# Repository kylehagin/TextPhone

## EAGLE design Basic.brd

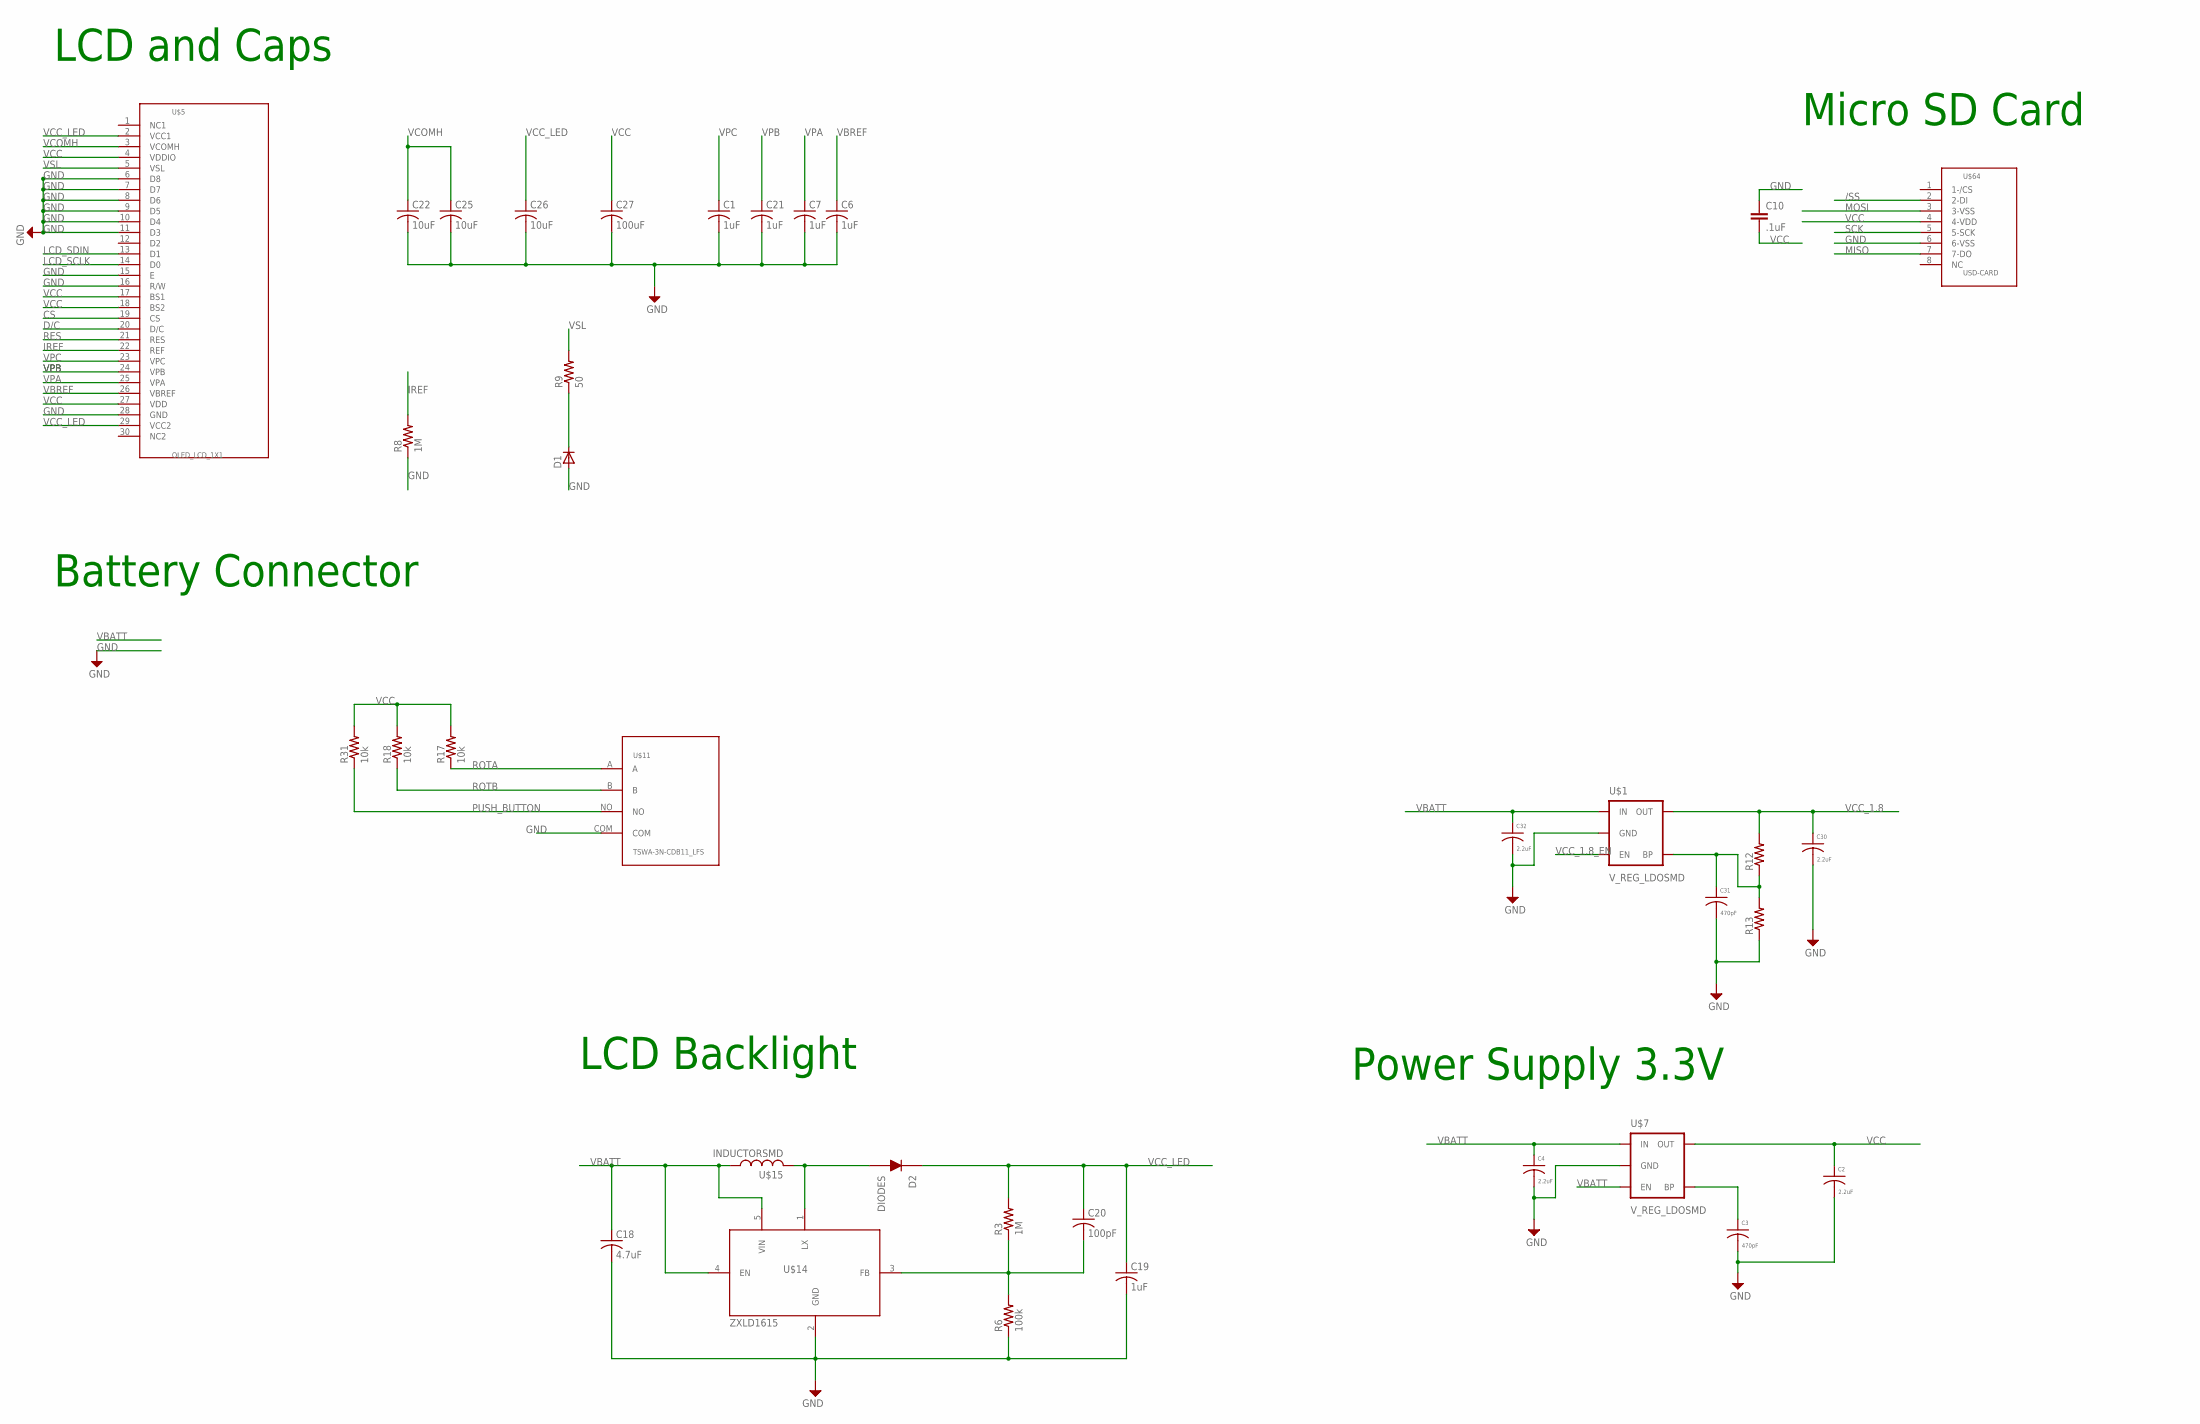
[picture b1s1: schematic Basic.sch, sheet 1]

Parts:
C1, C6, C7, C21: 1uF; C0402
C2, C4: 2.2uF; C0402
C3, C31: 470pF; C0402
C10: .1uF; C0402
C18: 4.7uF; C0805K
C19: 1uF; C1206
C20: 100pF; C0402
C22, C25, C26: 10uF; C0603
C27: 100uF; C0603
C30, C32: 2.2uF; C0603
D1: D-SOD123; SOD123
D2: DIODES; SOD-123
R3: 1M; R0805
R6: 100k; R0805
R8: 1M; R0603
R9: 50; R0603
R12, R13: R-US_R0402; R0402
R17, R18, R31: 10k; R0402
U$1, U$7: V_REG_LDOSMD; SOT23-5
U$5: OLED_LCD_1X1; 30ZIF
U$11: TSWA-3N-CDB11_LFS; TSWA-3N-CB11_LFS
U$14: ZXLD1615; SOT23-5L
U$15: INDUCTORSMD; INDUCTORSMD1
U$64: USD-CARD; 502774-0891

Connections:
/SS: U$64.2 (2-DI); also elsewhere on the board
CS: U$5.19 (CS); also elsewhere on the board
D/C: U$5.20 (D/C); also elsewhere on the board
GND: C1.2, C2.2, C3.2, C4.2, C6.2, C7.2, C10.1, C18.2, C19.2, C21.2, C22.2, C25.2, C26.2, C27.2, C30.2, C31.2, C32.2, D1.2 (A), R6.1, R8.1, R13.1, U$1.2 (GND), U$5.6 (D8), U$5.7 (D7), U$5.8 (D6), U$5.9 (D5), U$5.10 (D4), U$5.11 (D3), U$5.15 (E), U$5.16 (R/W), U$5.28 (GND), U$7.2 (GND), U$11.COM, U$14.2 (GND), U$64.6 (6-VSS); also elsewhere on the board
IREF: R8.2, U$5.22 (REF)
LCD_SCLK: U$5.14 (D0); also elsewhere on the board
LCD_SDIN: U$5.13 (D1); also elsewhere on the board
MISO: U$64.7 (7-DO); also elsewhere on the board
MOSI: U$64.3 (3-VSS); also elsewhere on the board
unnamed: C3.1, U$7.4 (BP)
unnamed: C20.2, R3.1, R6.2, U$14.3 (FB)
unnamed: D1.1 (C), R9.1
unnamed: D2.1 (A1), U$14.1 (LX), U$15.2
unnamed: C31.1, R12.1, R13.2, U$1.4 (BP)
PUSH_BUTTON: R31.1, U$11.NO; also elsewhere on the board
RES: U$5.21 (RES); also elsewhere on the board
ROTA: R17.1, U$11.A; also elsewhere on the board
ROTB: R18.1, U$11.B; also elsewhere on the board
SCK: U$64.5 (5-SCK); also elsewhere on the board
VBATT: C4.1, C18.1, C32.1, U$1.1 (IN), U$7.1 (IN), U$7.3 (EN), U$14.4 (EN), U$14.5 (VIN), U$15.1; also elsewhere on the board
VBREF: C6.1, U$5.26 (VBREF)
VCC: C2.1, C10.2, C27.1, R17.2, R18.2, R31.2, U$5.4 (VDDIO), U$5.17 (BS1), U$5.18 (BS2), U$5.27 (VDD), U$7.5 (OUT), U$64.4 (4-VDD); also elsewhere on the board
VCC_1.8: C30.1, R12.2, U$1.5 (OUT); also elsewhere on the board
VCC_1.8_EN: U$1.3 (EN); also elsewhere on the board
VCC_LED: C19.1, C20.1, C26.1, D2.2 (C), R3.2, U$5.2 (VCC1), U$5.29 (VCC2)
VCOMH: C22.1, C25.1, U$5.3 (VCOMH)
VPA: C7.1, U$5.25 (VPA)
VPB: C21.1, U$5.24 (VPB)
VPC: C1.1, U$5.23 (VPC)
VSL: R9.2, U$5.5 (VSL)

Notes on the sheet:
Battery Connector
Power Supply 3.3V
LCD Backlight
LCD and Caps
Micro SD Card

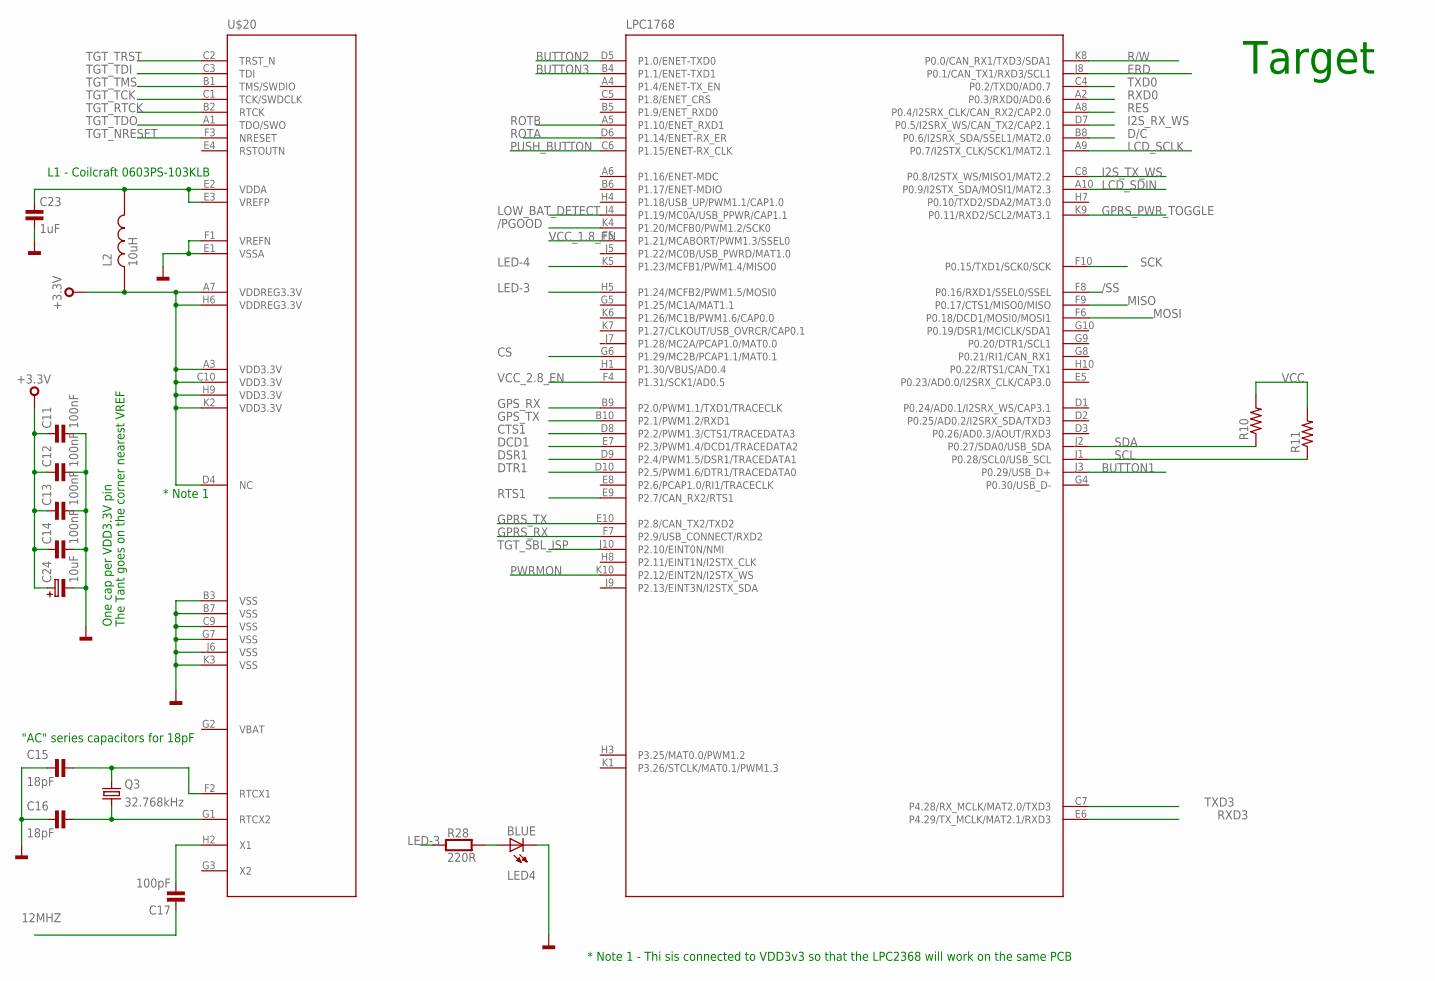
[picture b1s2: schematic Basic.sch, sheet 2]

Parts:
C11, C12, C13, C14: 100nF; 0402
C15, C16: 18pF; 0402
C17: 100pF; 0402
C23: 1uF; 0805
C24: 10uF; C106B
L2: 10uH; L0603
LED4: BLUE; LED_0805
Q3: 32.768kHz; FC135
R10, R11: R-US_R0402; R0402
R28: 220R; 0402
U$20: LPC1768; TFBGA100

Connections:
12MHZ: C17.1; also elsewhere on the board
/PGOOD: U$20.K4 (P1.20/MCFB0/PWM1.2/SCK0)
/SS: U$20.F8 (P0.16/RXD1/SSEL0/SSEL); also elsewhere on the board
BUTTON1: U$20.J3 (P0.29/USB_D+)
BUTTON2: U$20.D5 (P1.0/ENET-TXD0)
BUTTON3: U$20.B4 (P1.1/ENET-TXD1)
CS: U$20.G6 (P1.29/MC2B/PCAP1.1/MAT0.1); also elsewhere on the board
CTS1: U$20.D8 (P2.2/PWM1.3/CTS1/TRACEDATA3)
D/C: U$20.B8 (P0.6/I2SRX_SDA/SSEL1/MAT2.0); also elsewhere on the board
DCD1: U$20.E7 (P2.3/PWM1.4/DCD1/TRACEDATA2)
DSR1: U$20.D9 (P2.4/PWM1.5/DSR1/TRACEDATA1)
DTR1: U$20.D10 (P2.5/PWM1.6/DTR1/TRACEDATA0)
ERD: U$20.J8 (P0.1/CAN_TX1/RXD3/SCL1)
GND: C11.2, C12.2, C13.2, C14.2, C15.1, C16.1, C23.2, C24.2, LED4.K, U$20.B3 (VSS), U$20.B7 (VSS), U$20.C9 (VSS), U$20.E1 (VSSA), U$20.F1 (VREFN), U$20.G7 (VSS), U$20.J6 (VSS), U$20.K3 (VSS); also elsewhere on the board
GPRS_PWR_TOGGLE: U$20.K9 (P0.11/RXD2/SCL2/MAT3.1); also elsewhere on the board
GPRS_RX: U$20.F7 (P2.9/USB_CONNECT/RXD2); also elsewhere on the board
GPRS_TX: U$20.E10 (P2.8/CAN_TX2/TXD2); also elsewhere on the board
GPS_RX: U$20.B9 (P2.0/PWM1.1/TXD1/TRACECLK); also elsewhere on the board
GPS_TX: U$20.B10 (P2.1/PWM1.2/RXD1); also elsewhere on the board
I2S_RX_WS: U$20.D7 (P0.5/I2SRX_WS/CAN_TX2/CAP2.1)
I2S_TX_WS: U$20.C8 (P0.8/I2STX_WS/MISO1/MAT2.2)
IC6_RTC1: C15.2, Q3.X2 (2), U$20.F2 (RTCX1)
IC6_RTC2: C16.2, Q3.X1 (1), U$20.G1 (RTCX2)
IC6_XTAL1: C17.2, U$20.H2 (X1)
LCD_SCLK: U$20.A9 (P0.7/I2STX_CLK/SCK1/MAT2.1); also elsewhere on the board
LCD_SDIN: U$20.A10 (P0.9/I2STX_SDA/MOSI1/MAT2.3); also elsewhere on the board
LED-3: R28.1, U$20.H5 (P1.24/MCFB2/PWM1.5/MOSI0)
LED-4: U$20.K5 (P1.23/MCFB1/PWM1.4/MISO0)
LOW_BAT_DETECT: U$20.J4 (P1.19/MC0A/USB_PPWR/CAP1.1)
MISO: U$20.F9 (P0.17/CTS1/MISO0/MISO); also elsewhere on the board
MOSI: U$20.F6 (P0.18/DCD1/MOSI0/MOSI1); also elsewhere on the board
unnamed: LED4.A, R28.2
unnamed: C23.1, L2.P$2, U$20.E2 (VDDA), U$20.E3 (VREFP)
PUSH_BUTTON: U$20.C6 (P1.15/ENET-RX_CLK); also elsewhere on the board
PWRMON: U$20.K10 (P2.12/EINT2N/I2STX_WS); also elsewhere on the board
R/W: U$20.K8 (P0.0/CAN_RX1/TXD3/SDA1)
RES: U$20.A8 (P0.4/I2SRX_CLK/CAN_RX2/CAP2.0); also elsewhere on the board
ROTA: U$20.D6 (P1.14/ENET-RX_ER); also elsewhere on the board
ROTB: U$20.A5 (P1.10/ENET_RXD1); also elsewhere on the board
RTS1: U$20.E9 (P2.7/CAN_RX2/RTS1)
RXD0: U$20.A2 (P0.3/RXD0/AD0.6); also elsewhere on the board
RXD3: U$20.E6 (P4.29/TX_MCLK/MAT2.1/RXD3)
SCK: U$20.F10 (P0.15/TXD1/SCK0/SCK); also elsewhere on the board
SCL: R11.1, U$20.J1 (P0.28/SCL0/USB_SCL)
SDA: R10.1, U$20.J2 (P0.27/SDA0/USB_SDA)
TGT_NRESET: U$20.F3 (NRESET); also elsewhere on the board
TGT_RTCK: U$20.B2 (RTCK)
TGT_SBL_ISP: U$20.J10 (P2.10/EINT0N/NMI); also elsewhere on the board
TGT_TCK: U$20.C1 (TCK/SWDCLK)
TGT_TDI: U$20.C3 (TDI)
TGT_TDO: U$20.A1 (TDO/SWO)
TGT_TMS: U$20.B1 (TMS/SWDIO)
TGT_TRST: U$20.C2 (TRST_N)
TXD0: U$20.C4 (P0.2/TXD0/AD0.7); also elsewhere on the board
TXD3: U$20.C7 (P4.28/RX_MCLK/MAT2.0/TXD3)
VCC: C11.1, C12.1, C13.1, C14.1, C24.1, L2.P$1, R10.2, R11.2, U$20.A3 (VDD3.3V), U$20.A7 (VDDREG3.3V), U$20.C10 (VDD3.3V), U$20.D4 (NC), U$20.H6 (VDDREG3.3V), U$20.H9 (VDD3.3V), U$20.K2 (VDD3.3V); also elsewhere on the board
VCC_1.8_EN: U$20.F5 (P1.21/MCABORT/PWM1.3/SSEL0); also elsewhere on the board
VCC_2.8_EN: U$20.F4 (P1.31/SCK1/AD0.5)

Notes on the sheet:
The Tant goes on the corner nearest VREF
L1 - Coilcraft 0603PS-103KLB
"AC" series capacitors for 18pF
One cap per VDD3.3V pin
Target
* Note 1
* Note 1 - Thi sis connected to VDD3v3 so that the LPC2368 will work on the same PCB

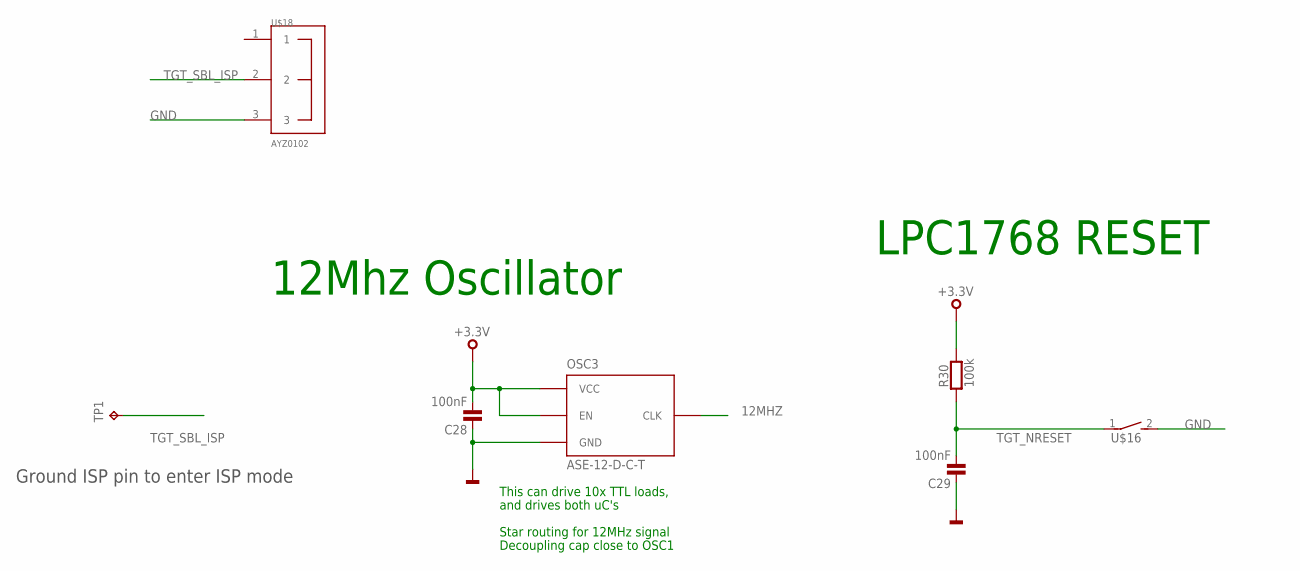
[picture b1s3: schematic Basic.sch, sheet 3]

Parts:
C28, C29: 100nF; 0402
OSC3: ASE-12-D-C-T; OSC3.2X.2.5
R30: 100k; 0402
TP1: TPTP09R; TP09R
U$16: RGHT-ANGLE-SMT-SWITCH-688-SKRELF; 2.9X3.9X2.0
U$18: AYZ0102

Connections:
12MHZ: OSC3.P$3 (CLK); also elsewhere on the board
GND: C28.1, C29.1, OSC3.P$2 (GND), U$16.2, U$18.3; also elsewhere on the board
TGT_NRESET: C29.2, R30.1, U$16.1; also elsewhere on the board
TGT_SBL_ISP: TP1.TP, U$18.2; also elsewhere on the board
VCC: C28.2, OSC3.P$1 (EN), OSC3.P$4 (VCC), R30.2; also elsewhere on the board

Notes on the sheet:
Ground ISP pin to enter ISP mode
This can drive 10x TTL loads,
and drives both uC's
Star routing for 12MHz signal
Decoupling cap close to OSC1
12Mhz Oscillator
LPC1768 RESET

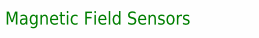
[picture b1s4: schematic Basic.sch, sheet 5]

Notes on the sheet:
Magnetic Field Sensors

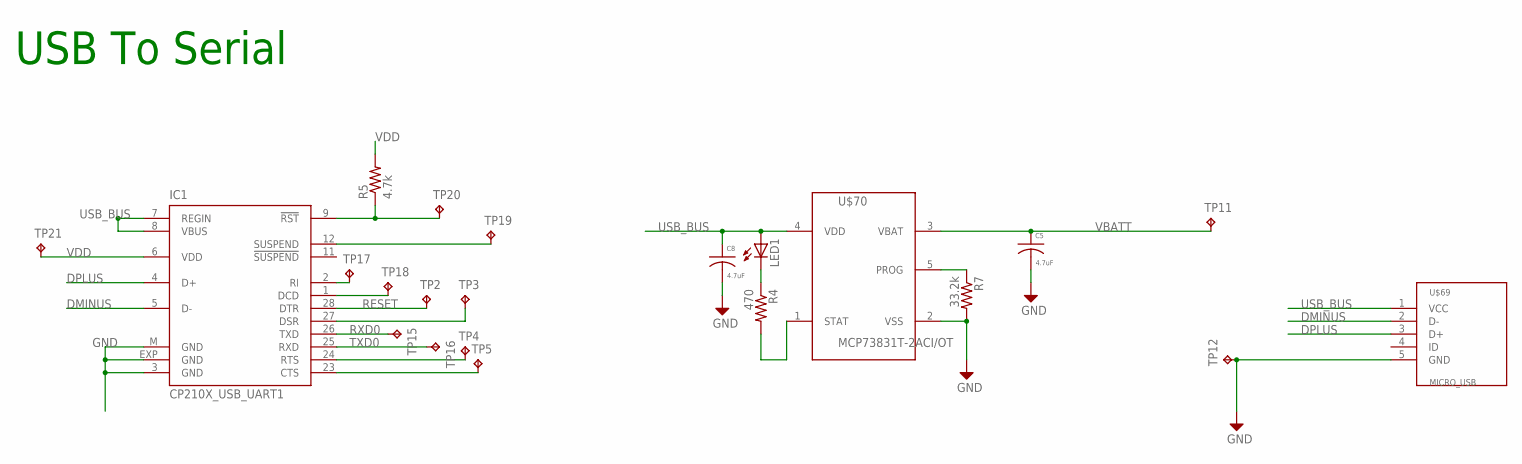
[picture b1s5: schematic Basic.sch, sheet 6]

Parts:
C5, C8: 4.7uF; C0603
IC1: CP210X_USB_UART1; MLP28
LED1: LEDCHIP-LED0603; CHIP-LED0603
R4: 470; R0402
R5: 4.7k; R0402
R7: 33.2k; R0402
TP2, TP3, TP4, TP5, TP15, TP16, TP17, TP18, TP19, TP20, TP21: TPTP06R; TP06R
TP11, TP12: TPTP20SQ; TP20SQ
U$69: MICRO_USB
U$70: MCP73831T-2ACI/OT; SOT23-5L

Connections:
CHG_STAT: R4.2, U$70.1 (STAT)
DMINUS: IC1.5 (D-), U$69.2 (D-)
DPLUS: IC1.4 (D+), U$69.3 (D+)
GND: C5.2, C8.2, IC1.3 (GND), IC1.EXP (GND), IC1.M (GND), R7.2, TP12.TP, U$69.5 (GND), U$70.2 (VSS); also elsewhere on the board
unnamed: IC1.9 (!RST), R5.1, TP20.TP
unnamed: IC1.24 (RTS), TP4.TP
unnamed: IC1.23 (CTS), TP5.TP
unnamed: IC1.27 (DSR), TP3.TP
unnamed: IC1.2 (RI), TP17.TP
unnamed: IC1.1 (DCD), TP18.TP
unnamed: IC1.12 (SUSPEND), TP19.TP
unnamed: LED1.C, R4.1
unnamed: R7.1, U$70.5 (PROG)
RESET: IC1.28 (DTR), TP2.TP
RXD0: IC1.26 (TXD), TP15.TP; also elsewhere on the board
TXD0: IC1.25 (RXD), TP16.TP; also elsewhere on the board
USB_BUS: C8.1, IC1.7 (REGIN), IC1.8 (VBUS), LED1.A, U$69.1 (VCC), U$70.4 (VDD)
VBATT: C5.1, TP11.TP, U$70.3 (VBAT); also elsewhere on the board
VDD: IC1.6 (VDD), R5.2, TP21.TP

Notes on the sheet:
USB To Serial

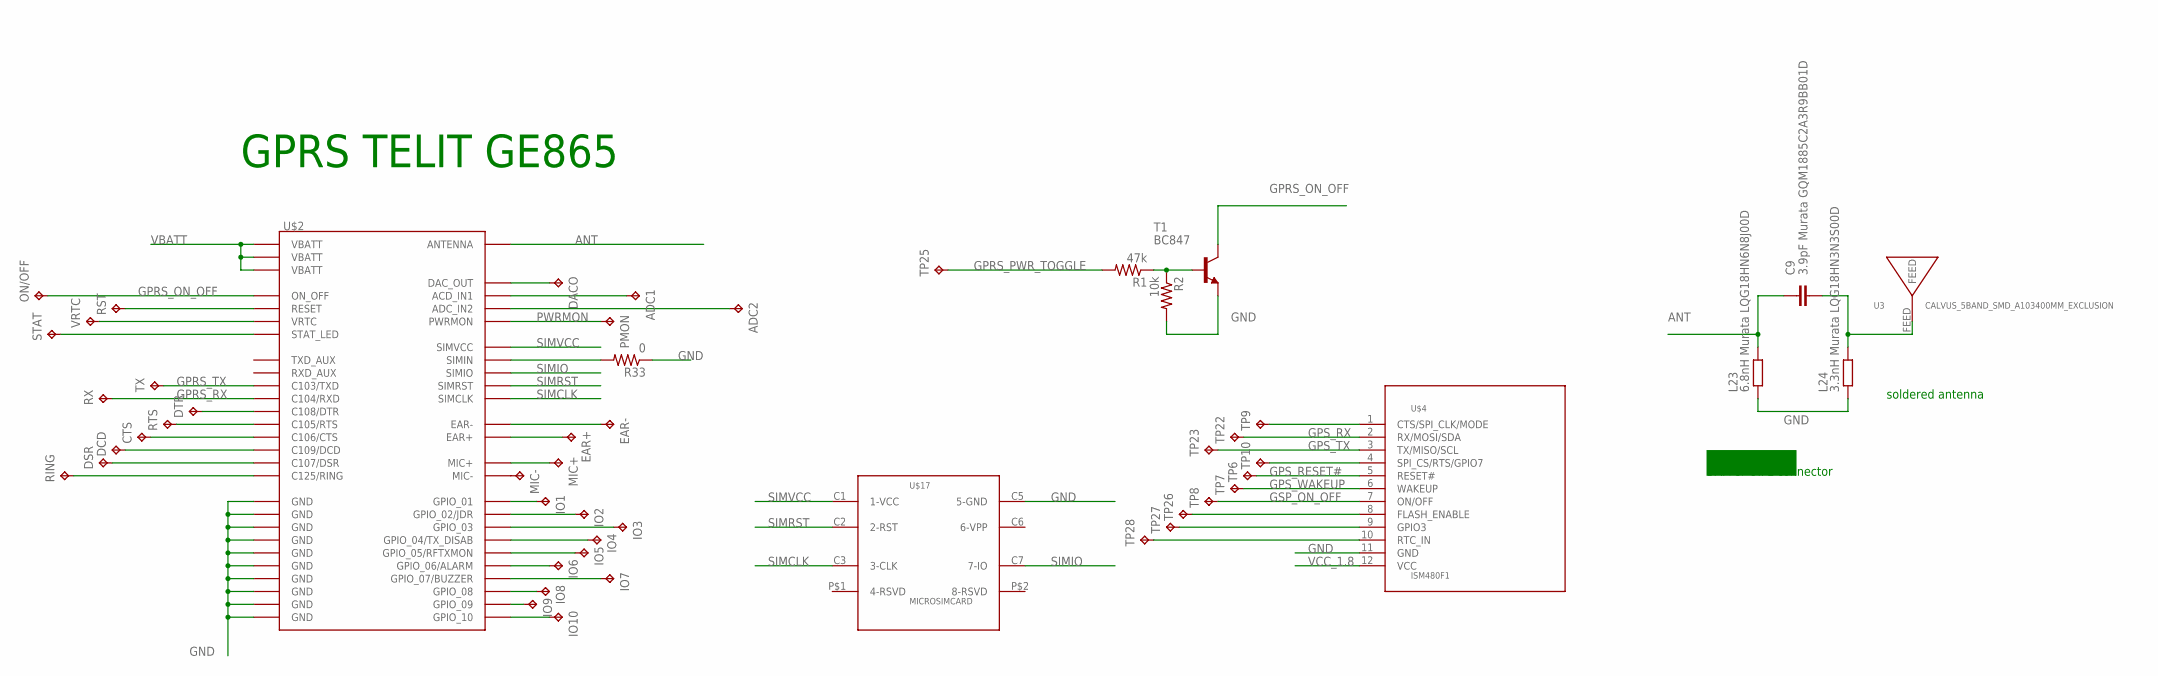
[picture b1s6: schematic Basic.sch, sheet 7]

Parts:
ADC1, ADC2: TPTP06R; TP06R
C9: 3.9pF Murata GQM1885C2A3R9BB01D; C0603-ROUND
CTS: TPTP06R; TP06R
DACO: TPTP06R; TP06R
DCD: TPTP06R; TP06R
DSR: TPTP06R; TP06R
DTR: TPTP06R; TP06R
EAR+: TPTP06R; TP06R
EAR-: TPTP06R; TP06R
IO1, IO2, IO3, IO4, IO5, IO6, IO7, IO8, IO9, IO10: TPTP06R; TP06R
L23: 6.8nH Murata LQG18HN6N8J00D; R0603-ROUND
L24: 3.3nH Murata LQG18HN3N3S00D; R0603-ROUND
MIC+: TPTP06R; TP06R
MIC-: TPTP06R; TP06R
ON/OFF: TPTP06R; TP06R
PMON: TPTP06R; TP06R
R1: 47k; R0402
R2: 10k; R0402
R33: 0; R0402
RING: TPTP06R; TP06R
RST: TPTP06R; TP06R
RTS: TPTP06R; TP06R
RX: TPTP06R; TP06R
STAT: TPTP06R; TP06R
T1: BC847; SOT23
TP6, TP7, TP8, TP9, TP10, TP22, TP23, TP25, TP26, TP27, TP28: TPTP06R; TP06R
TX: TPTP06R; TP06R
U3: CALVUS_5BAND_SMD_A103400MM_EXCLUSION; CALVUS_5BAND_SMD_A10340_0MM_EXCLUSION
U$2: GE865
U$4: ISM480F1; 20488-012E-01
U$17: MICROSIMCARD; FMS006-5000-0
VRTC: TPTP06R; TP06R

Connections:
ANT: C9.1, L23.2, U$2.H5 (ANTENNA)
ANTENA: C9.2, L24.2, U3.FEED
GND: L23.1, L24.1, R2.2, R33.1, T1.2 (E), U$2.C2 (GND), U$2.C7 (GND), U$2.E5 (GND), U$2.E7 (GND), U$2.G1 (GND), U$2.G3 (GND), U$2.G4 (GND), U$2.G5 (GND), U$2.H3 (GND), U$2.H6 (GND), U$4.11 (GND), U$17.C5 (5-GND); also elsewhere on the board
GPRS_ON_OFF: ON/OFF.TP, T1.3 (C), U$2.B1 (ON_OFF)
GPRS_PWR_TOGGLE: R1.2, TP25.TP; also elsewhere on the board
GPRS_RX: RX.TP, U$2.A4 (C104/RXD); also elsewhere on the board
GPRS_TX: TX.TP, U$2.A3 (C103/TXD); also elsewhere on the board
GPS_RESET#: TP6.TP, U$4.5 (RESET#)
GPS_RX: TP22.TP, U$4.2 (RX/MOSI/SDA); also elsewhere on the board
GPS_TX: TP23.TP, U$4.3 (TX/MISO/SCL); also elsewhere on the board
GPS_WAKEUP: TP7.TP, U$4.6 (WAKEUP)
GSP_ON_OFF: TP8.TP, U$4.7 (ON/OFF)
unnamed: R33.2, U$2.B7 (SIMIN)
unnamed: R1.1, R2.1, T1.1 (B)
unnamed: RST.TP, U$2.C1 (RESET)
unnamed: U$2.H2 (VRTC), VRTC.TP
unnamed: STAT.TP, U$2.G8 (STAT_LED)
unnamed: EAR-.TP, U$2.E8 (EAR-)
unnamed: TP9.TP, U$4.1 (CTS/SPI_CLK/MODE)
unnamed: EAR+.TP, U$2.D8 (EAR+)
unnamed: MIC+.TP, U$2.B8 (MIC+)
unnamed: MIC-.TP, U$2.C8 (MIC-)
unnamed: TP10.TP, U$4.4 (SPI_CS/RTS/GPIO7)
unnamed: IO7.TP, U$2.G6 (GPIO_07/BUZZER)
unnamed: IO6.TP, U$2.H8 (GPIO_06/ALARM)
unnamed: IO5.TP, U$2.G2 (GPIO_05/RFTXMON)
unnamed: IO8.TP, U$2.D4 (GPIO_08)
unnamed: IO9.TP, U$2.F4 (GPIO_09)
unnamed: DTR.TP, U$2.B3 (C108/DTR)
unnamed: RING.TP, U$2.B4 (C125/RING)
unnamed: DSR.TP, U$2.B2 (C107/DSR)
unnamed: DCD.TP, U$2.B5 (C109/DCD)
unnamed: CTS.TP, U$2.A2 (C106/CTS)
unnamed: RTS.TP, U$2.A1 (C105/RTS)
unnamed: TP26.TP, U$4.8 (FLASH_ENABLE)
unnamed: TP27.TP, U$4.9 (GPIO3)
unnamed: TP28.TP, U$4.10 (RTC_IN)
unnamed: IO1.TP, U$2.D3 (GPIO_01)
unnamed: IO2.TP, U$2.D2 (GPIO_02/JDR)
unnamed: IO3.TP, U$2.E4 (GPIO_03)
unnamed: IO4.TP, U$2.H7 (GPIO_04/TX_DISAB)
unnamed: DACO.TP, U$2.G7 (DAC_OUT)
unnamed: ADC1.TP, U$2.F5 (ACD_IN1)
unnamed: ADC2.TP, U$2.F6 (ADC_IN2)
unnamed: IO10.TP, U$2.E3 (GPIO_10)
PWRMON: PMON.TP, U$2.E2 (PWRMON); also elsewhere on the board
SIMCLK: U$2.A5 (SIMCLK), U$17.C3 (3-CLK)
SIMIO: U$2.A6 (SIMIO), U$17.C7 (7-IO)
SIMRST: U$2.A8 (SIMRST), U$17.C2 (2-RST)
SIMVCC: U$2.A7 (SIMVCC), U$17.C1 (1-VCC)
VBATT: U$2.F1 (VBATT), U$2.F2 (VBATT), U$2.F3 (VBATT); also elsewhere on the board
VCC_1.8: U$4.12 (VCC); also elsewhere on the board

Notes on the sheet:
GPRS TELIT GE865
soldered antenna
SMA or U.FL connector

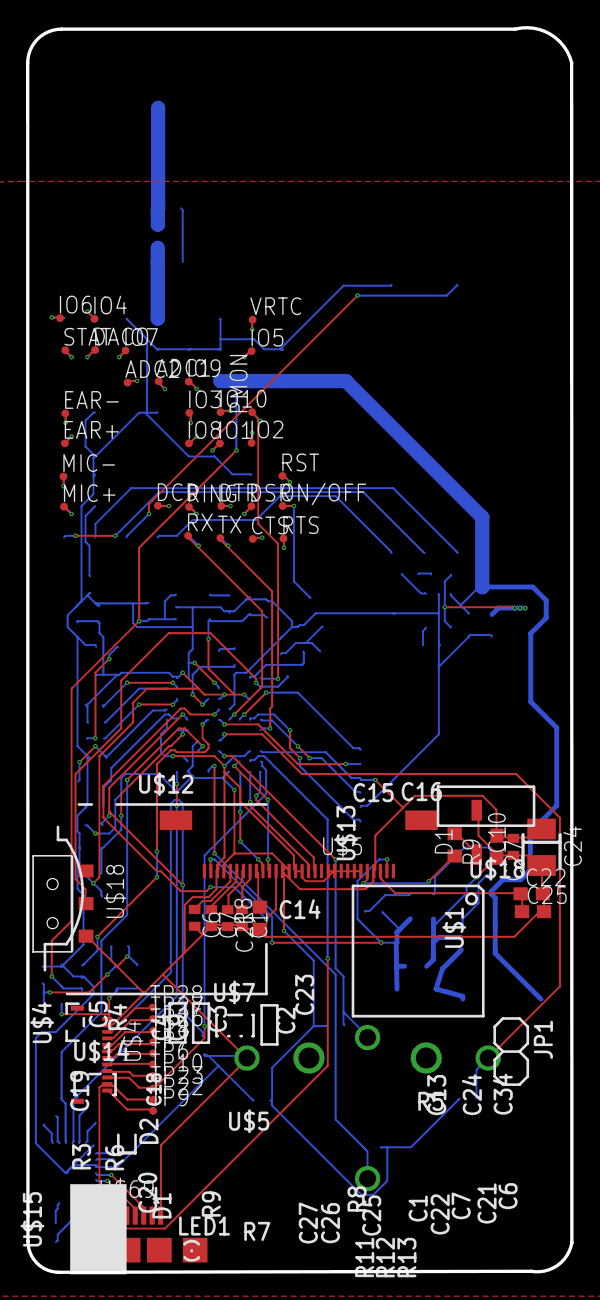
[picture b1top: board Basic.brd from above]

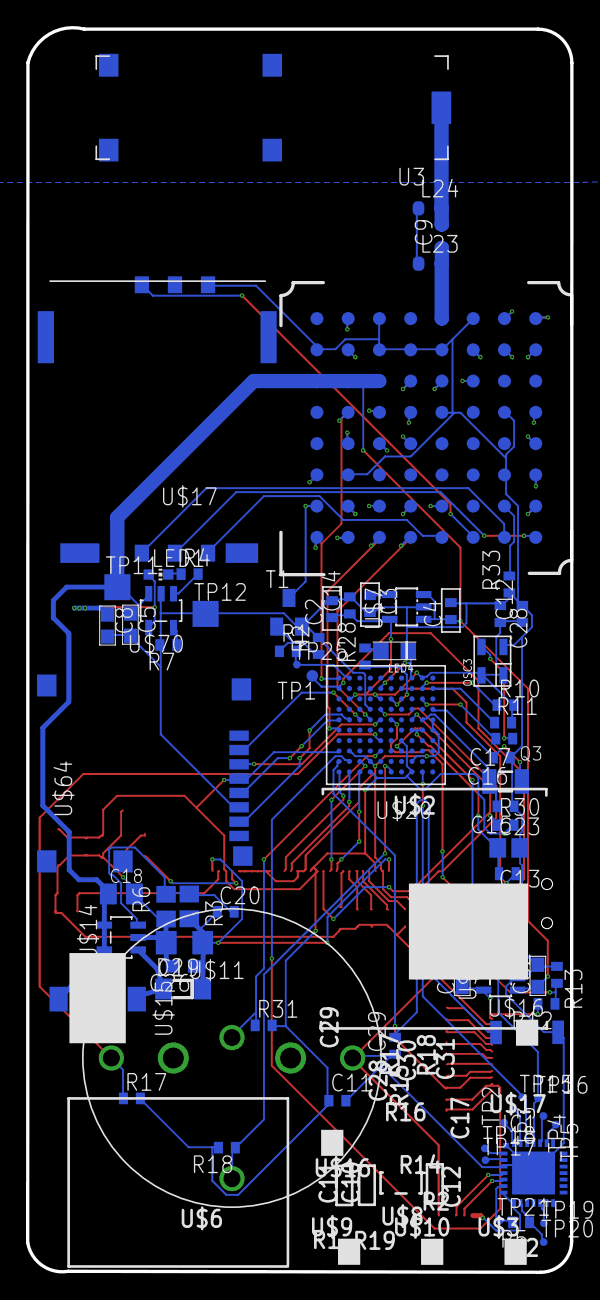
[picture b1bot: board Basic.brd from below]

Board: 4 copper layers, 41.8 x 95.5 mm, 133 parts (77 on the bottom side), 107 nets.
